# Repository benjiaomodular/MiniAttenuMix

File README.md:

# MiniAttenuMix

[![CC BY-SA 4.0][cc-by-sa-shield]][cc-by-sa]

A CV mixer with attenuverted inputs.

# Dependencies
- Made with Kicad v6.
- Install my [KiCAD Libraries](https://github.com/benjiaomodular/KiCadLibraries).

# Changelog

## v0.3 LED Fix 2 (Unverified)
- Moved wiring of LED to the output of first mixing stage (Pin 1 of U3)
- Mistake on OpAmp setup for LED.

## v0.2 LED Fix (Does not work)
- Moved wiring of LED to the output of first mixing stage (Pin 1 of U3)
- Mistake on OpAmp setup for LED.

## v0.1 Initial Release (Does not work)
- LED doesn't function properly

# License

This work is licensed under a
[Creative Commons Attribution-ShareAlike 4.0 International License][cc-by-sa].

[![CC BY-SA 4.0][cc-by-sa-image]][cc-by-sa]

[cc-by-sa]: http://creativecommons.org/licenses/by-sa/4.0/
[cc-by-sa-image]: https://licensebuttons.net/l/by-sa/4.0/88x31.png
[cc-by-sa-shield]: https://img.shields.io/badge/License-CC%20BY--SA%204.0-lightgrey.svg

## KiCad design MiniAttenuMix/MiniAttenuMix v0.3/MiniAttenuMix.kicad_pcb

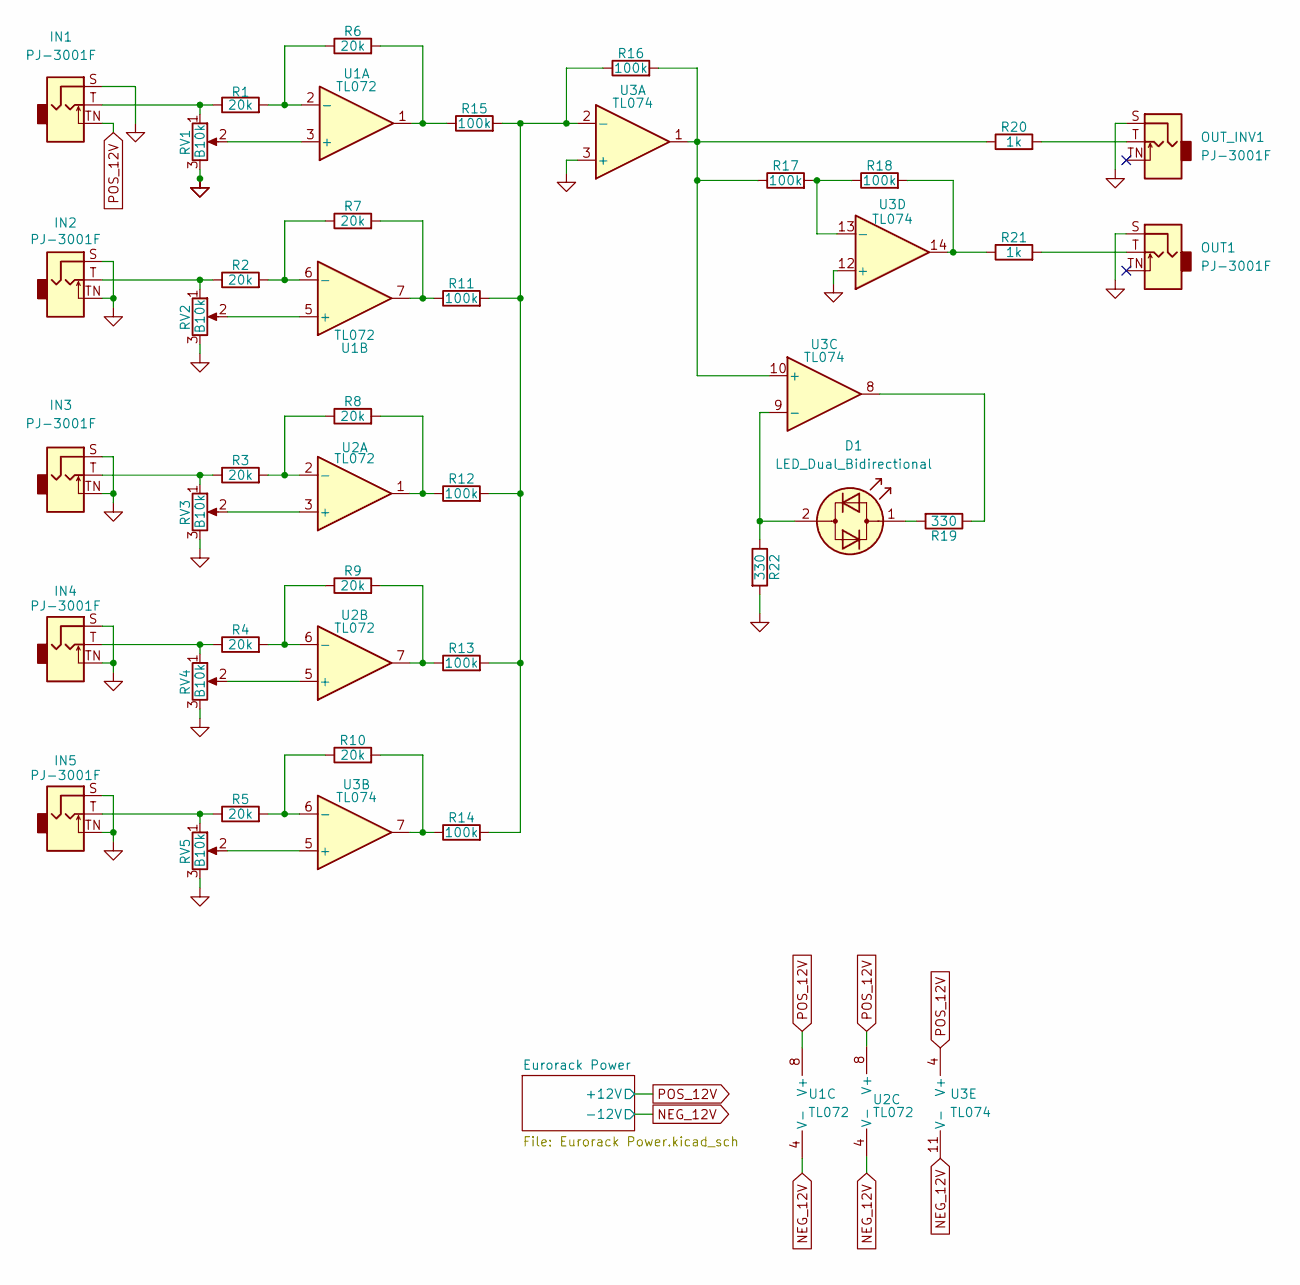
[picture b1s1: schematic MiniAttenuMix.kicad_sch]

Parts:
D1: LED_Dual_Bidirectional; LED_D3.0mm; Manufacturers Part Numb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 3ARG4HWC
IN1, IN2, IN3, IN4, IN5: PJ-3001F; AudioJack_3.5mm; Manufacturers Part Numb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 PJ-3001F
OUT1: PJ-3001F; AudioJack_3.5mm; Manufacturers Part Numb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 PJ-3001F
OUT_INV1: PJ-3001F; AudioJack_3.5mm; Manufacturers Part Numb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 PJ-3001F
R1, R2, R3, R4, R5, R6, R7, R8, R9, R10: 20k; R_0603_1608Metric_Pad0.98x0.95mm_HandSolder; Manufacturers Part Numb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 RC0603FR-0720KL
R11, R12, R13, R14, R15, R16, R17, R18: 100k; R_0603_1608Metric_Pad0.98x0.95mm_HandSolder; Manufacturers Part Numb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 RC0603FR-07100KL
R19, R22: 330; R_0603_1608Metric_Pad0.98x0.95mm_HandSolder; Manufacturers Part Numb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 CRG0603F330R
R20, R21: 1k; R_0603_1608Metric_Pad0.98x0.95mm_HandSolder; Manufacturers Part Numb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 RC0603FR-071KL
RV1, RV2, RV3, RV4, RV5: B10k; Potentiometer_RV09; Manufacturers Part Numb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 RD901F-40-15R1-B100K
U1, U2: TL072; SOIC-8_3.9x4.9mm_P1.27mm; Manufacturers Part Numb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 TL072CDT
U3: TL074; SOIC-14_3.9x8.7mm_P1.27mm; Manufacturers Part Numb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 TL074ACDT

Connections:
GND: IN1.S, IN2.S, IN2.TN, IN3.S, IN3.TN, IN4.S, IN4.TN, IN5.S, IN5.TN, OUT1.S, OUT_INV1.S, R22.2, RV1.3, RV2.3, RV3.3, RV4.3, RV5.3, U3.3 (+), U3.12 (+); also elsewhere on the board
NEG_12V: U1.4 (V-), U2.4 (V-), U3.11 (V-); also elsewhere on the board
unnamed: D1.1 (KA), R19.2
unnamed: D1.2 (AK), R22.1, U3.9 (-)
unnamed: IN1.T, R1.1, RV1.1
unnamed: IN2.T, R2.1, RV2.1
unnamed: IN3.T, R3.1, RV3.1
unnamed: IN4.T, R4.1, RV4.1
unnamed: IN5.T, R5.1, RV5.1
unnamed: OUT1.T, R21.2
unnamed: OUT_INV1.T, R20.2
unnamed: R1.2, R6.1, U1.2 (-)
unnamed: R2.2, R7.1, U1.6 (-)
unnamed: R3.2, R8.1, U2.2 (-)
unnamed: R4.2, R9.1, U2.6 (-)
unnamed: R5.2, R10.1, U3.6 (-)
unnamed: R10.2, R14.1, U3.7
unnamed: R7.2, R11.1, U1.7
unnamed: R11.2, R12.2, R13.2, R14.2, R15.2, R16.1, U3.2 (-)
unnamed: R8.2, R12.1, U2.1
unnamed: R9.2, R13.1, U2.7
unnamed: R6.2, R15.1, U1.1
unnamed: R17.2, R18.1, U3.13 (-)
unnamed: R18.2, R21.1, U3.14
unnamed: R19.1, U3.8
unnamed: RV1.2, U1.3 (+)
unnamed: RV2.2, U1.5 (+)
unnamed: RV3.2, U2.3 (+)
unnamed: RV4.2, U2.5 (+)
unnamed: RV5.2, U3.5 (+)
unnamed: R16.2, R17.1, R20.1, U3.1, U3.10 (+)
POS_12V: IN1.TN, U1.8 (V+), U2.8 (V+), U3.4 (V+); also elsewhere on the board

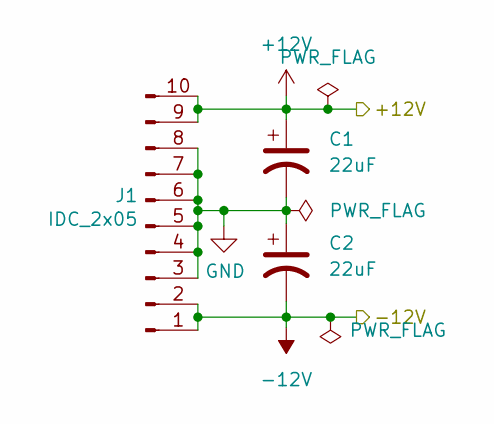
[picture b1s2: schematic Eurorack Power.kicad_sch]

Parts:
C1, C2: 22uF; C_0805_2012Metric_Pad1.18x1.45mm_HandSolder; Manufacturers Part Numb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 GRM21BR61E226ME44L
J1: IDC_2x05; IDC-Header_2x05_P2.54mm_Vertical; Manufacturers Part Numb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 X9555WV-2X05-6TV01; LCSC Part # C706914

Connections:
GND: C1.2, C2.1, J1.3, J1.4, J1.5, J1.6, J1.7, J1.8; also elsewhere on the board
NEG_12V: C2.2, J1.1, J1.2; also elsewhere on the board
POS_12V: C1.1, J1.9, J1.10; also elsewhere on the board

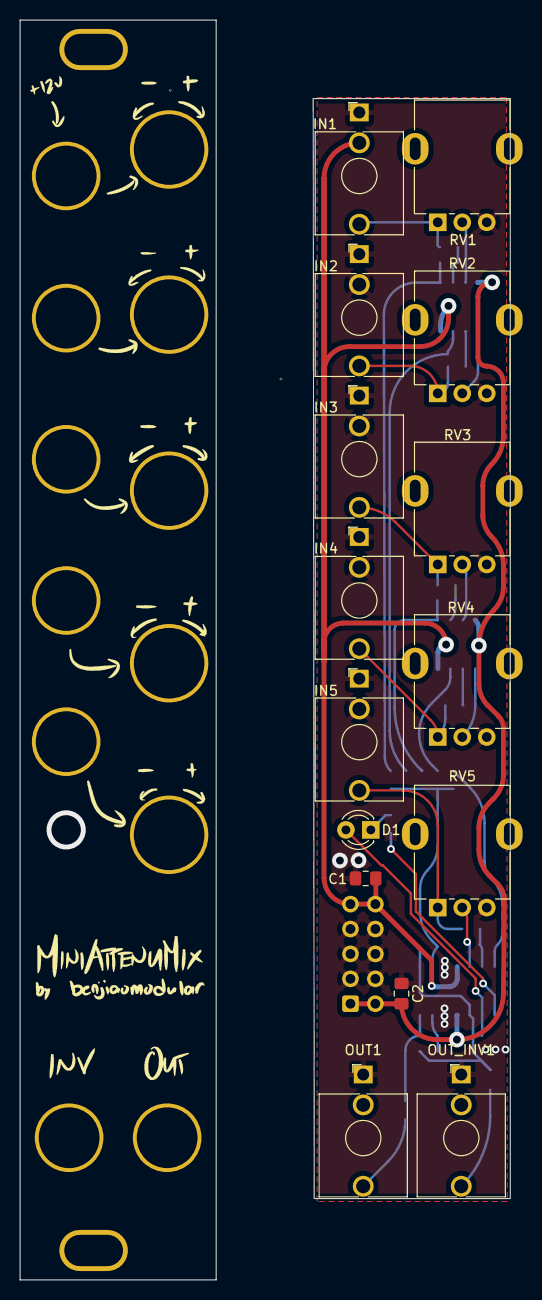
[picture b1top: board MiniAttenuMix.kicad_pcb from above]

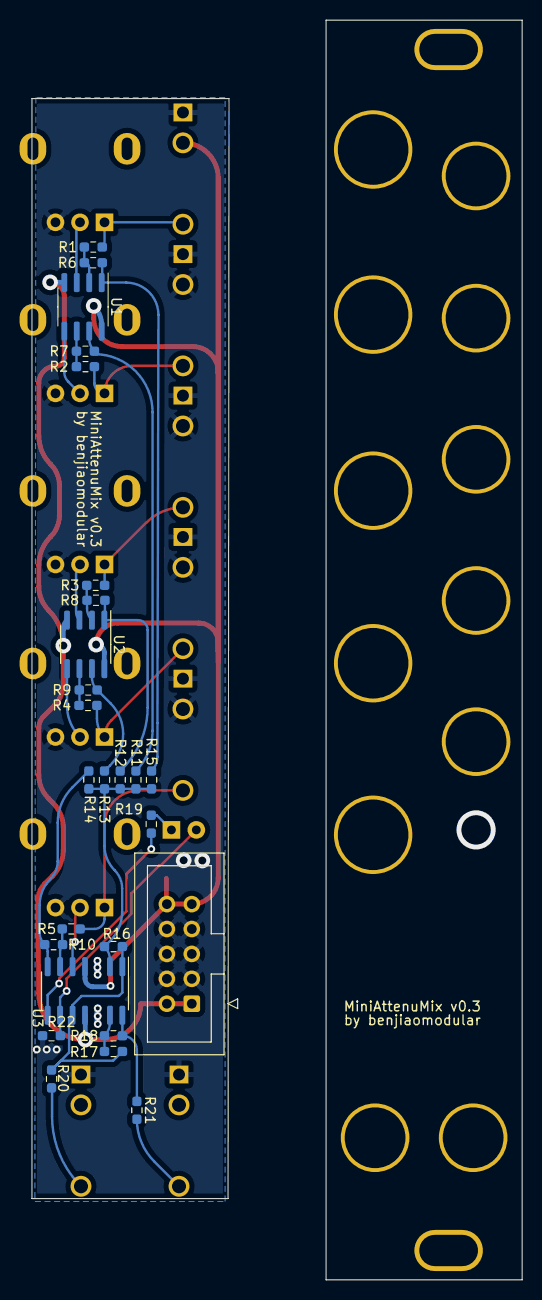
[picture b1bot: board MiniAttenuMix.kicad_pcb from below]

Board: 2 copper layers, 50.0 x 128.5 mm, 41 parts (26 on the bottom side), 32 nets.

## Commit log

2023-09-24 hello git
2023-10-10 Added pcb for v0.1
2023-11-08 Started v0.2
2023-11-08 Added unverified note
2023-11-22 Added v0.2 gerbers
2023-12-01 Added v0.3
2023-12-01 Updated schematics on docs
2023-12-01 updated v0.3 fabrication files
2024-04-10 Added license
